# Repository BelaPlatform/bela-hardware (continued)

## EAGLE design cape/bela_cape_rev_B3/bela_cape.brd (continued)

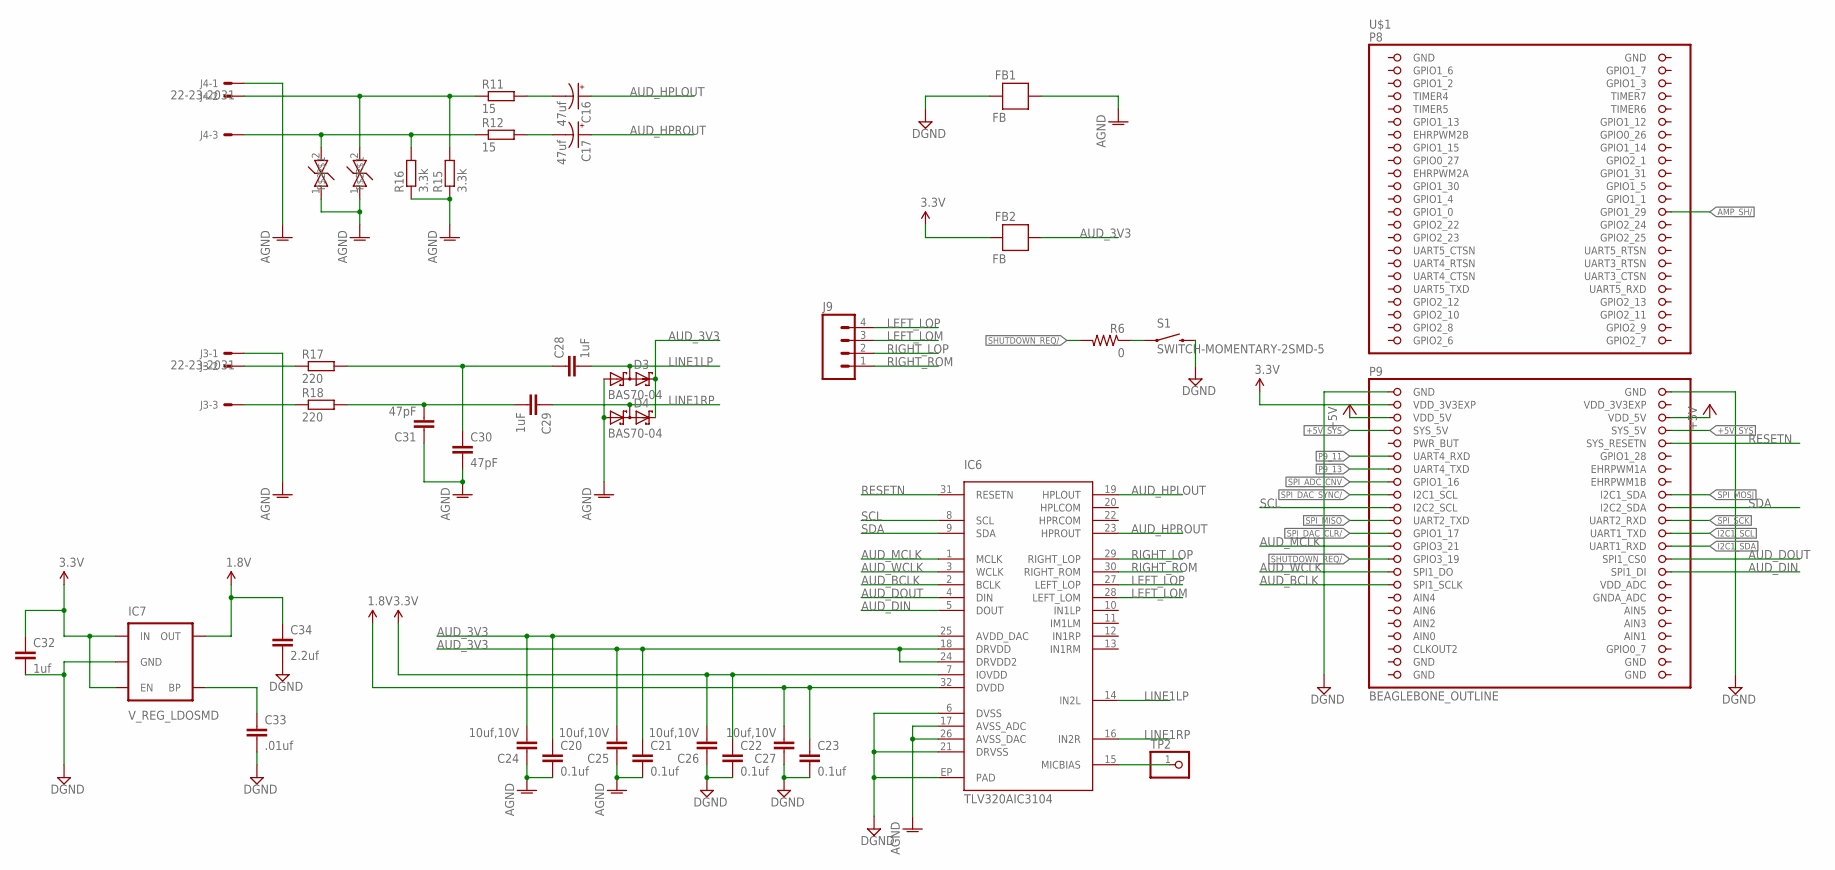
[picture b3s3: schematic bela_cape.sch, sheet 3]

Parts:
C16, C17: 47uf; EIA3216
C20, C21, C22, C23: 0.1uf; C0603
C24, C25, C26, C27: 10uf,10V; 0603-CAP
C28, C29: 1uF; C0603
C30, C31: 47pF; C0603
C32: 1uf; C0603
C33: .01uf; C0603
C34: 2.2uf; C0603
D1, D2: PGB0010603MR; 0603
D3, D4: BAS70-04; SOT23
FB1, FB2: FB; 0603
IC6: TLV320AIC3104; QFN-32
IC7: V_REG_LDOSMD; SOT23-5
J3, J4: 22-23-2031
J9: M04PTH; 1X04
R6: 0; R0603
R11, R12: 15; R0603
R15, R16: 3.3k; R0603
R17, R18: 220; R0603
S1: SWITCH-MOMENTARY-2SMD-5; TACTILE_SWITCH_SMD-4
TP2: PINHD-1X1; 1X01
U$1: BEAGLEBONE_OUTLINE; BEAGLEBONE_SHIELD

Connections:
1.8V: C23.1, C27.2, C34.1, IC6.32 (DVDD), IC7.5 (OUT)
3.3V: C22.1, C26.2, C32.1, FB2.2, IC6.7 (IOVDD), IC7.1 (IN), IC7.3 (EN), U$1.49 (VDD_3V3EXP); also elsewhere on the board
+5V_POW: U$1.51 (VDD_5V), U$1.52 (VDD_5V); also elsewhere on the board
+5V_SYS: U$1.53 (SYS_5V), U$1.54 (SYS_5V); also elsewhere on the board
AGND: C20.2, C21.2, C24.1, C25.1, C30.2, C31.1, D1.1, D2.1, D3.1 (A1), D4.1 (A1), FB1.1, IC6.17 (AVSS_ADC), IC6.26 (AVSS_DAC), J3.1, J4.1, R15.1, R16.1; also elsewhere on the board
AIN0: U$1.85 (AIN0)
AMP_SH/: U$1.26 (GPIO1_29); also elsewhere on the board
AUDIO_INL: C28.1, C30.1, R17.2
AUDIO_INR: C29.2, C31.2, R18.2
AUD_3V3: C20.1, C21.1, C24.2, C25.2, D3.2 (C2), D4.2 (C2), FB2.1, IC6.18 (DRVDD), IC6.24 (DRVDD2), IC6.25 (AVDD_DAC)
AUD_BCLK: IC6.2 (BCLK), U$1.77 (SPI1_SCLK)
AUD_DIN: IC6.5 (DOUT), U$1.76 (SPI1_DI)
AUD_DOUT: IC6.4 (DIN), U$1.74 (SPI1_CS0)
AUD_HPLOUT: C16.A (+), IC6.19 (HPLOUT)
AUD_HPROUT: C17.A (+), IC6.23 (HPROUT)
AUD_MCLK: IC6.1 (MCLK), U$1.71 (GPIO3_21)
AUD_WCLK: IC6.3 (WCLK), U$1.75 (SPI1_DO)
DGND: C22.2, C23.2, C26.1, C27.1, C32.2, C33.2, C34.2, FB1.2, IC6.6 (DVSS), IC6.21 (DRVSS), IC6.EP (PAD), IC7.2 (GND), S1.4 (2), U$1.1 (GND), U$1.2 (GND), U$1.47 (GND), U$1.48 (GND), U$1.89 (GND), U$1.90 (GND), U$1.91 (GND), U$1.92 (GND); also elsewhere on the board
HPL: D2.2, J4.2, R11.1, R15.2
HPR: D1.2, J4.3, R12.1, R16.2
I2C1_SCL: U$1.70 (UART1_TXD); also elsewhere on the board
I2C1_SDA: U$1.72 (UART1_RXD); also elsewhere on the board
LEFT_LOM: IC6.28 (LEFT_LOM), J9.3
LEFT_LOP: IC6.27 (LEFT_LOP), J9.4
LINE1LP: C28.2, D3.3 (C1A2), IC6.14 (IN2L)
LINE1RP: C29.1, D4.3 (C1A2), IC6.16 (IN2R)
unnamed: C16.C (-), R11.2
unnamed: IC6.15 (MICBIAS), TP2.1
unnamed: R6.1, S1.1
unnamed: C17.C (-), R12.2
unnamed: J3.2, R17.1
unnamed: C33.1, IC7.4 (BP)
unnamed: J3.3, R18.1
P9_11: U$1.57 (UART4_RXD)
P9_13: U$1.59 (UART4_TXD)
RESETN: IC6.31 (RESETN), U$1.56 (SYS_RESETN)
RIGHT_LOP: IC6.29 (RIGHT_LOP), J9.2
RIGHT_ROM: IC6.30 (RIGHT_ROM), J9.1
SCL: IC6.8 (SCL), U$1.65 (I2C2_SCL)
SDA: IC6.9 (SDA), U$1.66 (I2C2_SDA)
SHUTDOWN_REQ/: R6.2, U$1.73 (GPIO3_19)
SPI_ADC_CNV: U$1.61 (GPIO1_16); also elsewhere on the board
SPI_DAC_CLR/: U$1.69 (GPIO1_17); also elsewhere on the board
SPI_DAC_SYNC/: U$1.63 (I2C1_SCL); also elsewhere on the board
SPI_MISO: U$1.67 (UART2_TXD); also elsewhere on the board
SPI_MOSI: U$1.64 (I2C1_SDA); also elsewhere on the board
SPI_SCK: U$1.68 (UART2_RXD); also elsewhere on the board
VDD_3V3EXP: U$1.50 (VDD_3V3EXP)

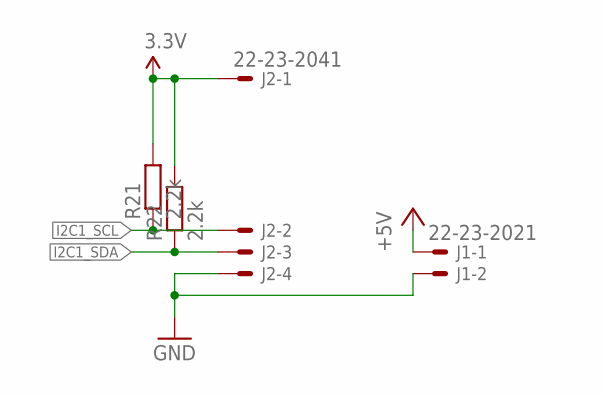
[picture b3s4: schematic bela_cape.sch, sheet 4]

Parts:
J1: 22-23-2021
J2: 22-23-2041
R21, R22: 2.2k; R0603

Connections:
3.3V: J2.1, R21.2, R22.2; also elsewhere on the board
+5V_AMP: J1.1; also elsewhere on the board
DGND: J1.2, J2.4; also elsewhere on the board
I2C1_SCL: J2.2, R21.1; also elsewhere on the board
I2C1_SDA: J2.3, R22.1; also elsewhere on the board

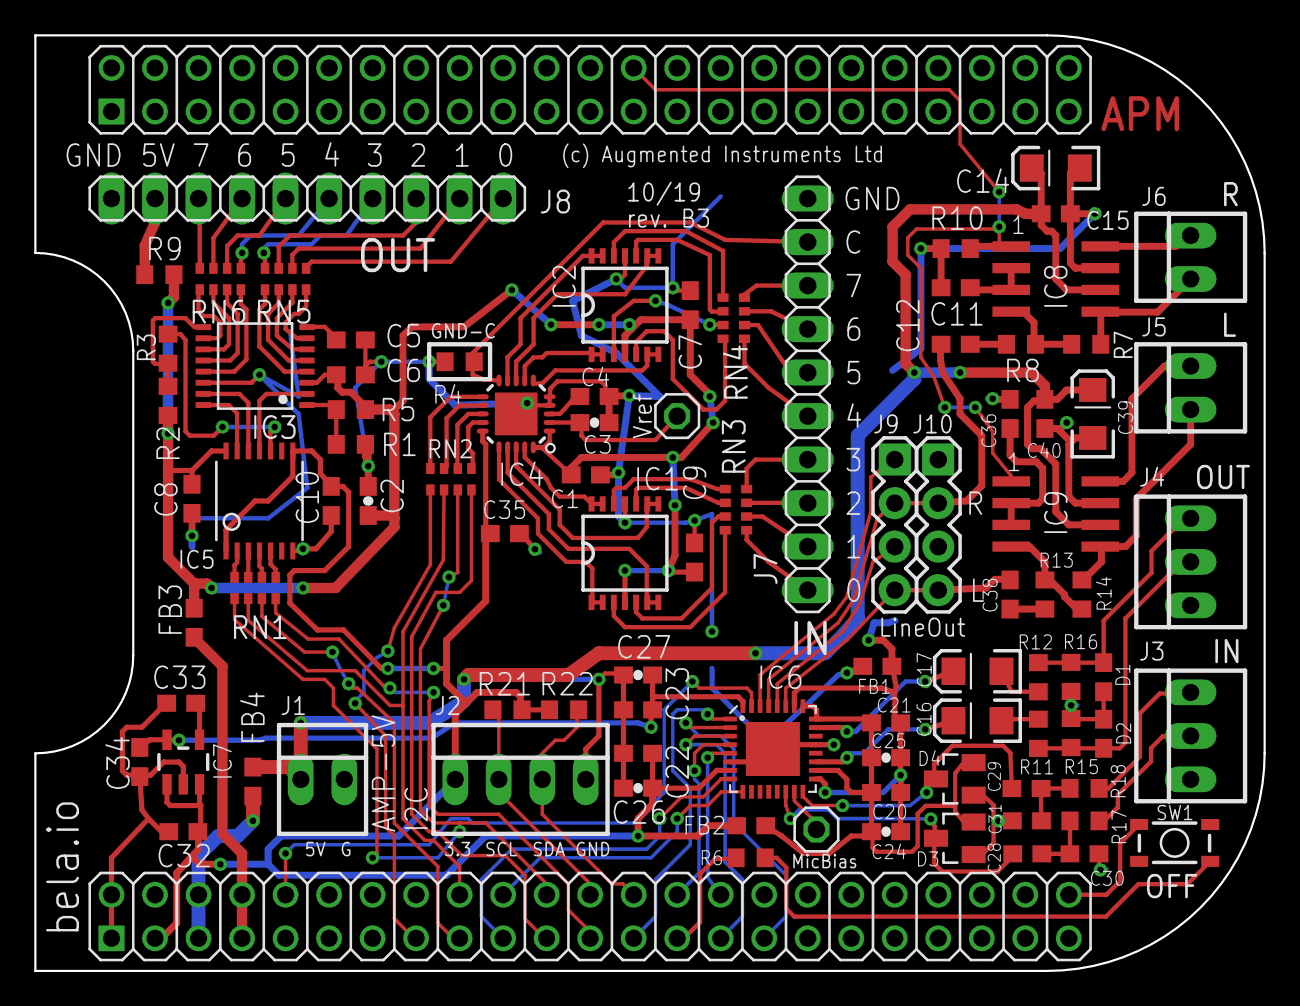
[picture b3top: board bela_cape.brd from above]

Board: 2 copper layers, 71.8 x 54.6 mm, 93 parts (0 on the bottom side), 117 nets.

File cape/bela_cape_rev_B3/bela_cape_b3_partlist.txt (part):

Partlist

Exported from bela_cape.brd at 09/12/2019 12:21

EAGLE Version 6.5.0 Copyright (c) 1988-2013 CadSoft

Assembly variant: 

Part     Value                   Package              Library             Position (inch)       Orientation

C1       0.1uF                   C0603                rcl                 (1.03 -1.71)          R0
C2       10uF                    0603-CAP             SparkFun-Passives   (0.53 -1.77)          R90
C3       10uF                    0603-CAP             SparkFun-Passives   (1.05 -1.59)          R0
C4       0.1uF                   C0603                rcl                 (1.05 -1.53)          R0
C5       0.1uF                   C0603                rcl                 (0.49 -1.4)           R0
C6       0.1uF                   C0603                rcl                 (0.49 -1.48)          R0
C7       0.1uF                   C0603                rcl                 (1.27 -1.32)          R90
C8       0.1uF                   C0603                rcl                 (0.125 -1.765)        R270
C9       0.1uF                   C0603                rcl                 (1.28 -1.9)           R90
C10      0.1uF                   C0603                rcl                 (0.445 -1.77)         R270
C11      0.1uF                   C0603                rcl                 (1.88 -1.28)          R180
C12      1uF                     C0603                rcl                 (1.88 -1.41)          R0
C14      47uF                    EIA3216              SparkFun-Capacitors (2.11 -1.005)         R180
C15      0.1uF                   C0603                rcl                 (2.11 -1.11)          R0
C16      47uf                    EIA3216              SparkFun-Capacitors (1.93 -2.27500209)    R180
C17      47uf                    EIA3216              SparkFun-Capacitors (1.93 -2.16136602)    R180
C20      0.1uf                   C0603                rcl                 (1.72 -2.44)          R0
C21      0.1uf                   C0603                rcl                 (1.72 -2.28)          R0
C22      0.1uf                   C0603                rcl                 (1.15 -2.35)          R180
C23      0.1uf                   C0603                rcl                 (1.15 -2.25)          R180
C24      10uf,10V                0603-CAP             SparkFun-Passives   (1.72 -2.53)          R180
C25      10uf,10V                0603-CAP             SparkFun-Passives   (1.72 -2.36)          R180
C26      10uf,10V                0603-CAP             SparkFun-Passives   (1.15 -2.43)          R0
C27      10uf,10V                0603-CAP             SparkFun-Passives   (1.15 -2.17)          R0
C28      1uF                     C0603                rcl                 (2.04452817 -2.58090391) R180
C29      1uF                     C0603                rcl                 (2.04271001 -2.43091191) R0
C30      47pF                    C0603                rcl                 (2.17589186 -2.58090404) R0
C31      47pF                    C0603                rcl                 (2.04368602 -2.50495792) R0
C32      1uf                     C0603                rcl                 (0.105 -2.53)         R180
C33      .01uf                   C0603                rcl                 (0.1 -2.235)          R180
C34      2.2uf                   C0603                rcl                 (0.005 -2.37)         R270
C35      0.1uF                   C0603                rcl                 (0.844 -1.845)        R0
C36      0.1uF                   C0603                rcl                 (2.005 -1.57)         R90
C38      1uF                     C0603                rcl                 (2.005 -1.985)        R90
C39      47uF                    EIA3216              SparkFun-Capacitors (2.195 -1.57)         R90
C40      0.1uF                   C0603                rcl                 (2.085 -1.57)         R270
D1       PGB0010603MR            0603                 CircuitCo           (2.22 -2.175)         R90
D2       PGB0010603MR            0603                 CircuitCo           (2.22 -2.305)         R270
D3       BAS70-04                SOT23                diode               (1.87799409 -2.54519993) R90
D4       BAS70-04                SOT23                diode               (1.87799409 -2.4088499) R90
FB1      FB                      0603                 SparkFun-Passives   (1.7 -2.15)           R180
FB2      FB                      0603                 SparkFun-Passives   (1.41 -2.5163659)     R180
FB3      FB                      0603                 SparkFun-Passives   (0.13 -2.05)          R270
FB4      FB                      0603                 SparkFun-Passives   (0.265 -2.415)        R90
IC1      ADD8704RU               TSSOP14              analog-devices      (1.12 -1.89)          R90
IC2      ADD8704RU               TSSOP14              analog-devices      (1.12 -1.32)          R90
IC3      AD5668                  TSSOP16-PW           custom              (0.27 -1.46)          R90
IC4      AD7699                  LFCSP20-LEADS        custom              (0.87 -1.57)          R180
IC5                              TSSOP14              SparkFun-DigitalIC  (0.28 -1.77)          R0
IC6      TLV320AIC3104           QFN-32               CircuitCo           (1.46 -2.34)          R270
IC7      V_REG_LDOSMD            SOT23-5              SparkFun-PowerIC    (0.105 -2.37)         R0
IC8      LM4876                  SO8                  custom              (2.11 -1.26)          R270
IC9      LM4876                  SO8                  custom              (2.11 -1.8)           R270
J1       22-23-2021              22-23-2021           con-molex           (0.425 -2.41)         R0
J2       22-23-2041              22-23-2041           con-molex           (0.88 -2.41)          R0
J3       22-23-2031              22-23-2031           con-molex           (2.42 -2.31)          R90
J4       22-23-2031              22-23-2031           con-molex           (2.42 -1.91)          R90
J5       22-23-2021              22-23-2021           con-molex           (2.42 -1.51)          R90
J6       22-23-2021              22-23-2021           con-molex           (2.42 -1.21)          R90
J7                               1X10                 pinhead             (1.54 -1.525)         R90
J8                               1X10                 pinhead             (0.39 -1.075)         R180
J9                               1X04                 SparkFun-Connectors (1.74 -1.675)         R270
J10                              1X04                 SparkFun-Connectors (1.84 -1.675)         R270
R1       0                       R0603                rcl                 (0.49 -1.64)          R0
R2       0                       R0603                rcl                 (0.07 -1.54)          R90
R3       DNI                     R0603                rcl                 (0.07 -1.42)          R270
R4       0                       R0603                rcl                 (0.74 -1.45)          R0
R5       DNI                     R0603                rcl                 (0.49 -1.56)          R180
R6       0                       R0603                rcl                 (1.40872281 -2.59002178) R180
R7       43k                     R0603                rcl                 (2.18 -1.41)          R180
R8       22k                     R0603                rcl                 (2.03 -1.41)          R180
R9       100                     R0603                rcl                 (0.05 -1.25)          R0
R10      22k                     R0603                rcl                 (1.88 -1.19)          R180
R11      15                      R0603                rcl                 (2.07 -2.305)         R90
R12      15                      R0603                rcl                 (2.07 -2.175)         R270
R13      22k                     R0603                rcl                 (2.085 -1.985)        R270
R14      43k                     R0603                rcl                 (2.17 -1.985)         R270
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
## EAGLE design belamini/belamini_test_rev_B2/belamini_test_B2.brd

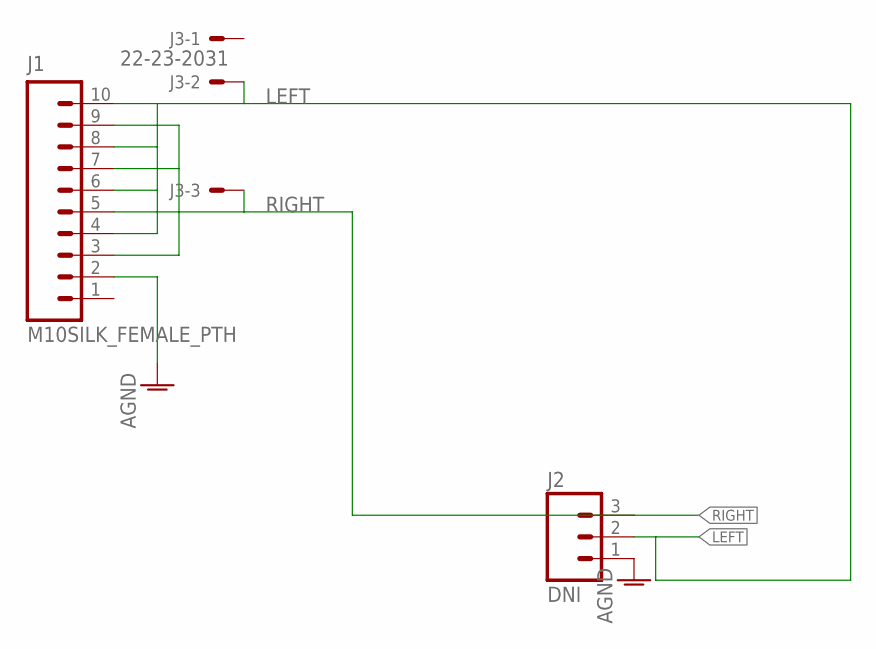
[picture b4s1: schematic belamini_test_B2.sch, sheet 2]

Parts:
J1: M10SILK_FEMALE_PTH; 1X10
J2: DNI; 1X03
J3: 22-23-2031

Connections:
AGND: J1.2
GND: J2.1
LEFT: J1.4, J1.6, J1.8, J1.10, J2.2, J3.2
RIGHT: J1.3, J1.5, J1.7, J1.9, J2.3, J3.3

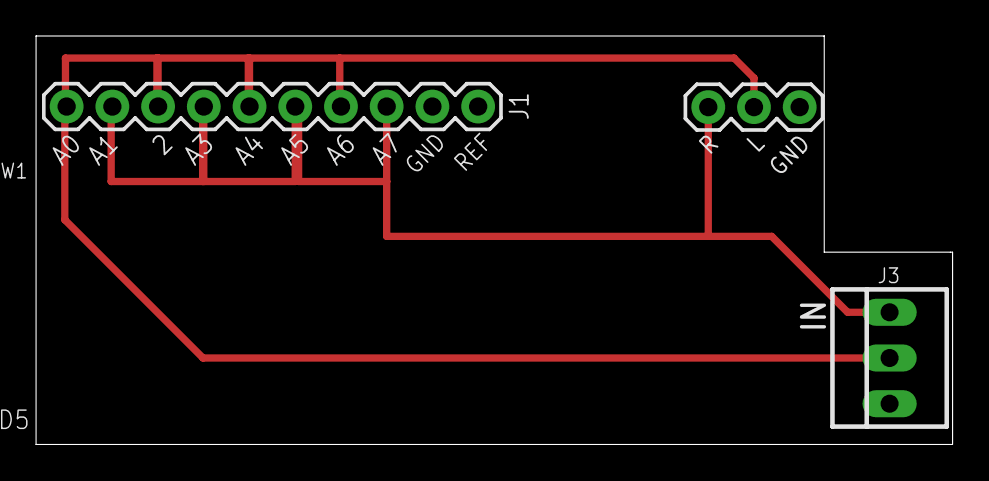
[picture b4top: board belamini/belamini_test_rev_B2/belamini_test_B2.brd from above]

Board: 2 copper layers, 50.9 x 22.7 mm, 3 parts (0 on the bottom side), 2 nets.

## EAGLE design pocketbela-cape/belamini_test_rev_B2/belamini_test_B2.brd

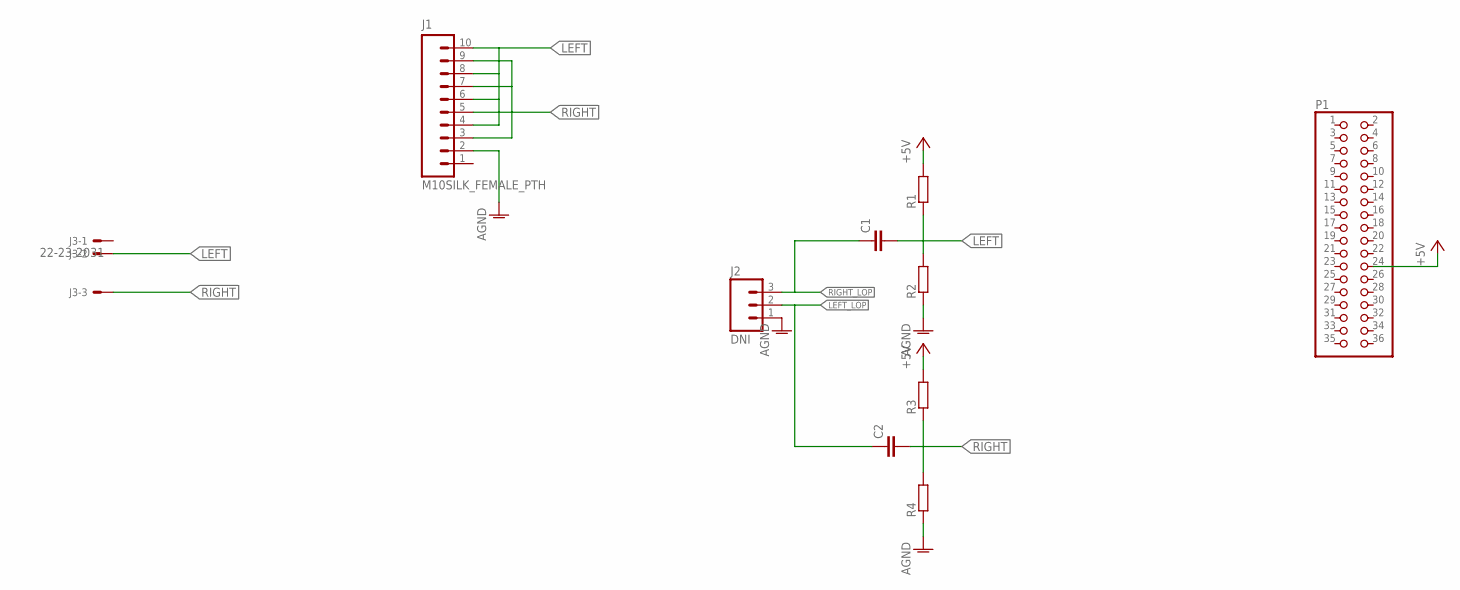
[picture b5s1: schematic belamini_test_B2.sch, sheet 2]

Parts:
C1, C2: C5/2.5; C5B2.5
J1: M10SILK_FEMALE_PTH; 1X10
J2: DNI; 1X03
J3: 22-23-2031
P1: PINHD-2X18; 2X18
R1, R2, R3, R4: R-EU_0204/7; 0204/7

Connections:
+5V_SYS: P1.24, R1.2, R3.2
AGND: J1.2, R2.1, R4.1
GND: J2.1
LEFT: C1.2, J1.4, J1.6, J1.8, J1.10, J3.2, R1.1, R2.2
LEFT_LOP: C2.1, J2.2
RIGHT: C2.2, J1.3, J1.5, J1.7, J1.9, J3.3, R3.1, R4.2
RIGHT_LOP: C1.1, J2.3

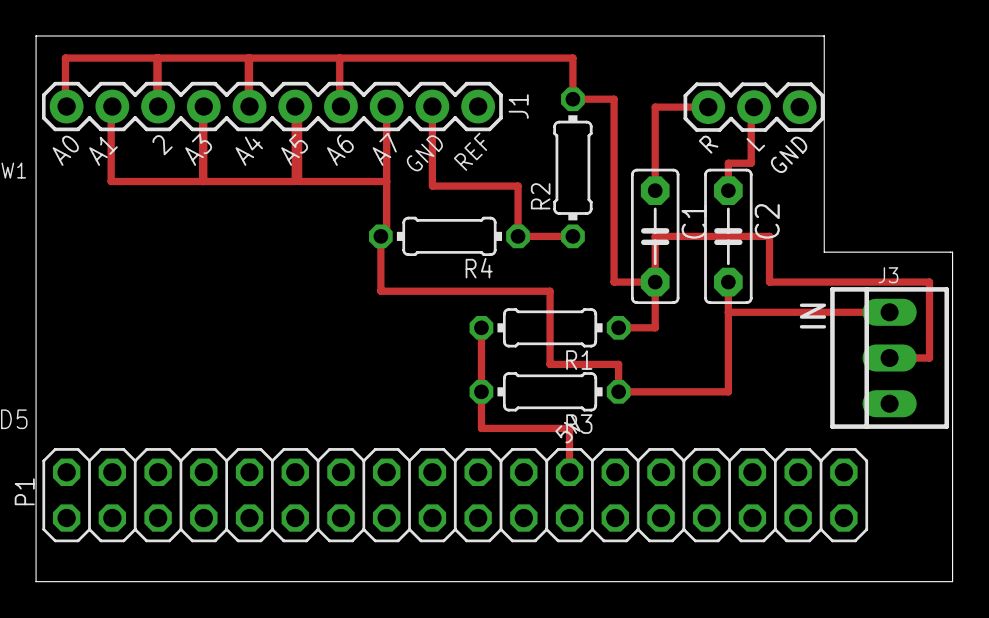
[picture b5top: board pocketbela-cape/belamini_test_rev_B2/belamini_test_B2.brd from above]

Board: 2 copper layers, 50.9 x 30.3 mm, 10 parts (0 on the bottom side), 6 nets.

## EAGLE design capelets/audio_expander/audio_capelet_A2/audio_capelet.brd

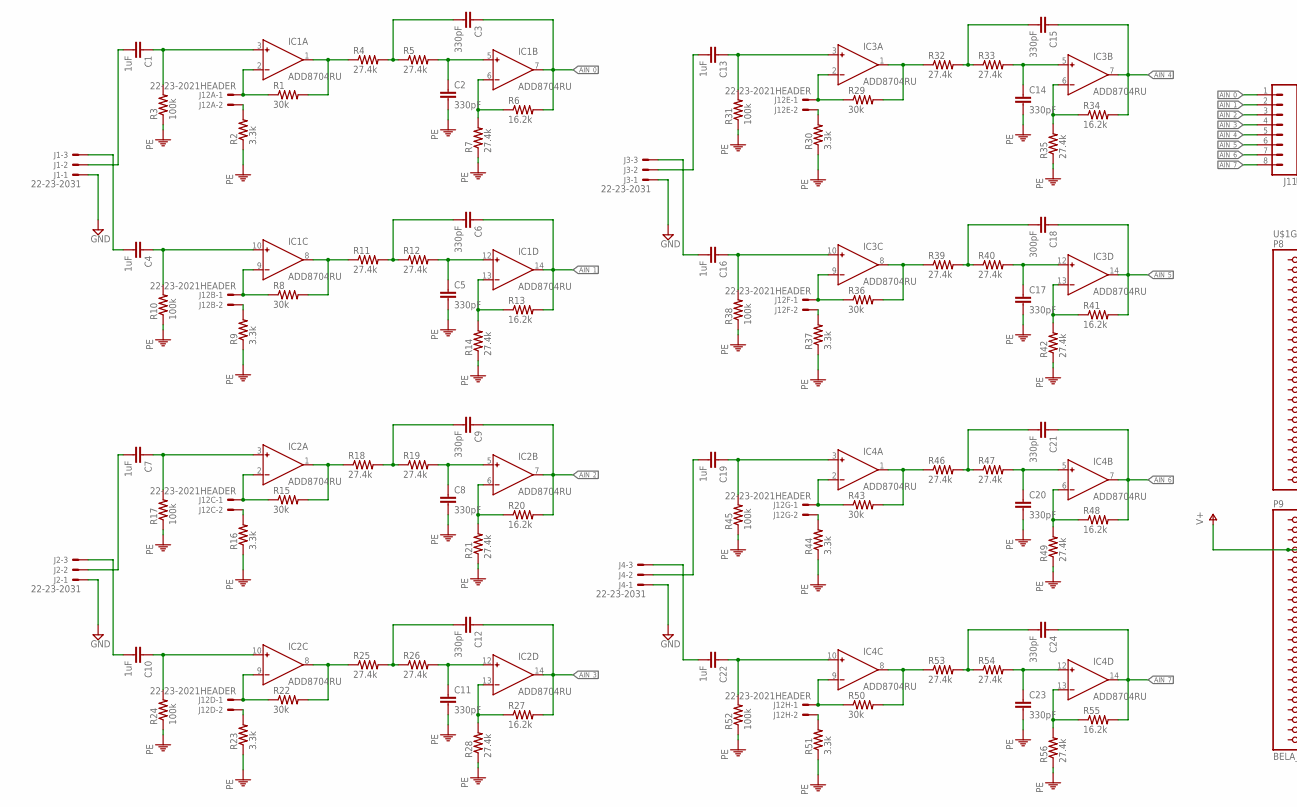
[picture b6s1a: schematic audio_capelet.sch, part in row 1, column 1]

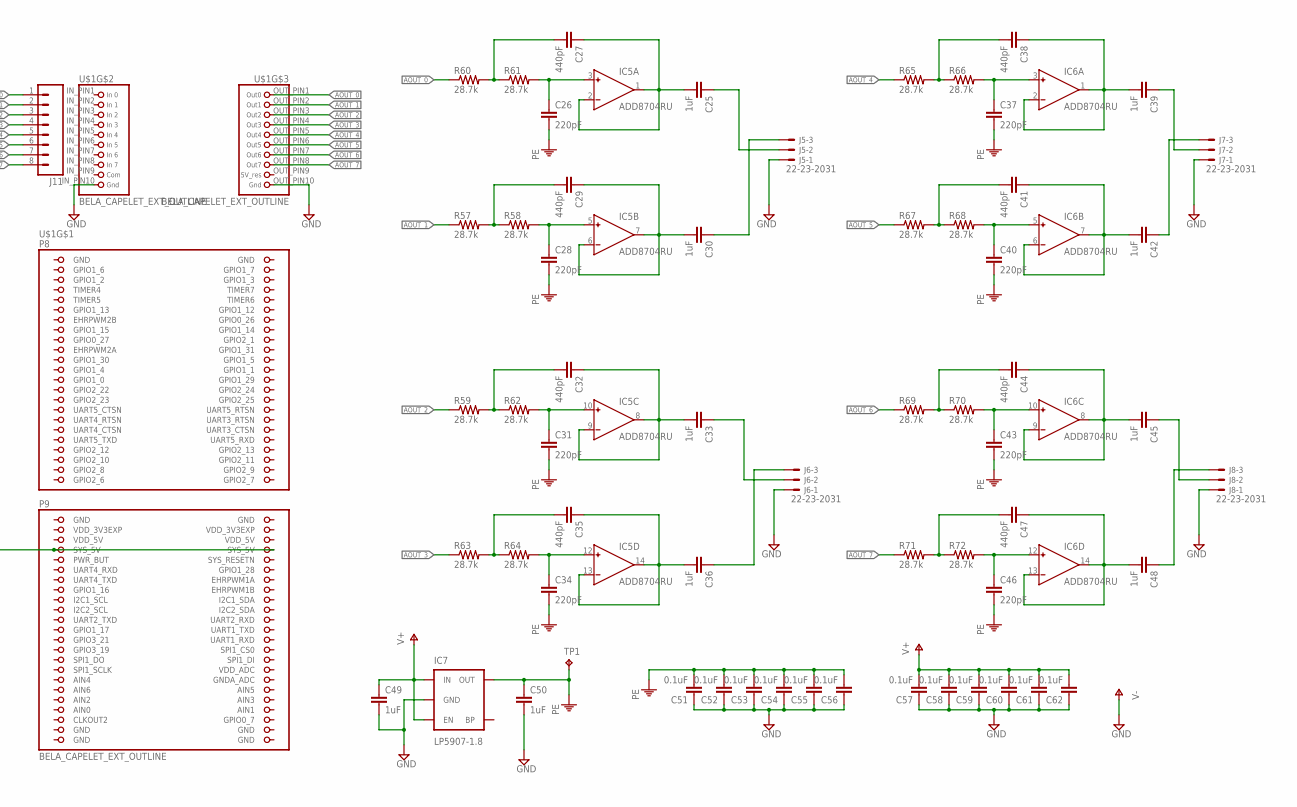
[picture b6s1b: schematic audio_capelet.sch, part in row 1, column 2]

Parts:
C1, C4, C7, C10, C13, C16, C19, C22, C25, C30, C33, C36, C39, C42, C45, C48, C49, C50: 1uF; C0603
C2, C3, C5, C6, C8, C9, C11, C12, C14, C15, C17, C20, C21, C23, C24: 330pF; C0603
C18: 300pF; C0603
C26, C28, C31, C34, C37, C40, C43, C46: 220pF; C0603
C27, C29, C32, C35, C38, C41, C44, C47: 440pF; C0603
C51, C52, C53, C54, C55, C56, C57, C58, C59, C60, C61, C62: 0.1uF; C0603
IC1, IC2, IC3, IC4, IC5, IC6: ADD8704RU; TSSOP14
IC7: LP5907-1.8; SOT23-5
J1, J2, J3, J4, J5, J6, J7, J8: 22-23-2031
J11: M08SMALL_DIAMETER; 1X08_SMALL_DIAMETER
J12A, J12B, J12C, J12D, J12E, J12F, J12G, J12H: 22-23-2021HEADER; 1X02
R1, R8, R15, R22, R29, R36, R43, R50: 30k; R0603
R2, R9, R16, R23, R30, R37, R44, R51: 3.3k; R0603
R3, R10, R17, R24, R31, R38, R45, R52: 100k; R0603
R4, R5, R7, R11, R12, R14, R18, R19, R21, R25, R26, R28, R32, R33, R35, R39, R40, R42, R46, R47, R49, R53, R54, R56: 27.4k; R0603
R6, R13, R20, R27, R34, R41, R48, R55: 16.2k; R0603
R57, R58, R59, R60, R61, R62, R63, R64, R65, R66, R67, R68, R69, R70, R71, R72: 28.7k; R0603
TP1: TPPAD1-17Y; P1-17Y
U$1: BELA_CAPELET_EXT_OUTLINE; BELA_CAPELET_EXTENDED_OUTLINE

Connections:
01: C30.1, J5.3
AIN0: U$1.85 (AIN0)
AIN_0: C3.1, IC1.7 (OUT), J11.1, R6.2
AIN_1: C6.1, IC1.14 (OUT), J11.2, R13.2
AIN_2: C9.1, IC2.7 (OUT), J11.3, R20.2
AIN_3: C12.1, IC2.14 (OUT), J11.4, R27.2
AIN_4: C15.1, IC3.7 (OUT), J11.5, R34.2
AIN_5: C18.1, IC3.14 (OUT), J11.6, R41.2
AIN_6: C21.1, IC4.7 (OUT), J11.7, R48.2
AIN_7: C24.1, IC4.14 (OUT), J11.8, R55.2
AOUT_0: R60.1, U$1.OUT_PIN1 (1)
AOUT_1: R57.1, U$1.OUT_PIN2 (2)
AOUT_2: R59.1, U$1.OUT_PIN3 (3)
AOUT_3: R63.1, U$1.OUT_PIN4 (4)
AOUT_4: R65.1, U$1.OUT_PIN5 (5)
AOUT_5: R67.1, U$1.OUT_PIN6 (6)
AOUT_6: R69.1, U$1.OUT_PIN7 (7)
AOUT_7: R71.1, U$1.OUT_PIN8 (8)
unnamed: C2.1, IC1.5 (IN+), R5.2
unnamed: IC1.2 (IN-), J12A.1, R1.1
unnamed: IC1.1 (OUT), R1.2, R4.1
unnamed: C3.2, R4.2, R5.1
unnamed: C25.2, C27.1, IC5.1 (OUT), IC5.2 (IN-)
unnamed: IC1.6 (IN-), R6.1, R7.2
unnamed: C1.1, IC1.3 (IN+), R3.2
unnamed: J12A.2, R2.2
unnamed: IC1.8 (OUT), R8.2, R11.1
unnamed: C6.2, R11.2, R12.1
unnamed: C5.1, IC1.12 (IN+), R12.2
unnamed: C27.2, R60.2, R61.1
unnamed: IC1.13 (IN-), R13.1, R14.2
unnamed: IC2.1 (OUT), R15.2, R18.1
unnamed: C4.1, IC1.10 (IN+), R10.2
unnamed: IC1.9 (IN-), J12B.1, R8.1
unnamed: C1.2, J1.2
unnamed: C4.2, J1.3
unnamed: IC2.2 (IN-), J12C.1, R15.1
unnamed: C9.2, R18.2, R19.1
unnamed: C8.1, IC2.5 (IN+), R19.2
unnamed: C26.1, IC5.3 (IN+), R61.2
unnamed: IC2.6 (IN-), R20.1, R21.2
unnamed: J12C.2, R16.2
unnamed: C7.1, IC2.3 (IN+), R17.2
unnamed: IC2.8 (OUT), R22.2, R25.1
unnamed: C12.2, R25.2, R26.1
unnamed: C11.1, IC2.12 (IN+), R26.2
unnamed: C29.2, R57.2, R58.1
unnamed: IC2.13 (IN-), R27.1, R28.2
unnamed: IC2.9 (IN-), J12D.1, R22.1
unnamed: J12D.2, R23.2
unnamed: C10.1, IC2.10 (IN+), R24.2
unnamed: C7.2, J2.2
unnamed: C10.2, J2.3
unnamed: IC3.1 (OUT), R29.2, R32.1
unnamed: C15.2, R32.2, R33.1
unnamed: C14.1, IC3.5 (IN+), R33.2
unnamed: C28.1, IC5.5 (IN+), R58.2
unnamed: IC3.6 (IN-), R34.1, R35.2
unnamed: C13.1, IC3.3 (IN+), R31.2
unnamed: IC3.2 (IN-), J12E.1, R29.1
unnamed: J12E.2, R30.2
unnamed: IC3.8 (OUT), R36.2, R39.1
unnamed: C18.2, R39.2, R40.1
unnamed: C17.1, IC3.12 (IN+), R40.2
unnamed: C29.1, C30.2, IC5.6 (IN-), IC5.7 (OUT)
unnamed: IC3.13 (IN-), R41.1, R42.2
unnamed: C16.1, IC3.10 (IN+), R38.2
unnamed: IC3.9 (IN-), J12F.1, R36.1
unnamed: J12F.2, R37.2
unnamed: C13.2, J3.2
unnamed: C16.2, J3.3
unnamed: IC4.1 (OUT), R43.2, R46.1
unnamed: C21.2, R46.2, R47.1
unnamed: C20.1, IC4.5 (IN+), R47.2
unnamed: C32.2, R59.2, R62.1
unnamed: IC4.6 (IN-), R48.1, R49.2
unnamed: C19.1, IC4.3 (IN+), R45.2
unnamed: IC4.2 (IN-), J12G.1, R43.1
unnamed: J12G.2, R44.2
unnamed: IC4.8 (OUT), R50.2, R53.1
unnamed: C24.2, R53.2, R54.1
unnamed: C23.1, IC4.12 (IN+), R54.2
unnamed: C31.1, IC5.10 (IN+), R62.2
unnamed: IC4.13 (IN-), R55.1, R56.2
unnamed: C22.1, IC4.10 (IN+), R52.2
unnamed: IC4.9 (IN-), J12H.1, R50.1
unnamed: J12H.2, R51.2
unnamed: C19.2, J4.2
unnamed: C22.2, J4.3
unnamed: C32.1, C33.2, IC5.8 (OUT), IC5.9 (IN-)
unnamed: C35.2, R63.2, R64.1
unnamed: C34.1, IC5.12 (IN+), R64.2
unnamed: C35.1, C36.2, IC5.13 (IN-), IC5.14 (OUT)
unnamed: C38.2, R65.2, R66.1
unnamed: C37.1, IC6.3 (IN+), R66.2
unnamed: J12B.2, R9.2
unnamed: C38.1, C39.2, IC6.1 (OUT), IC6.2 (IN-)
unnamed: C41.2, R67.2, R68.1
unnamed: C40.1, IC6.5 (IN+), R68.2
unnamed: C41.1, C42.2, IC6.6 (IN-), IC6.7 (OUT)
unnamed: C44.2, R69.2, R70.1
unnamed: C43.1, IC6.10 (IN+), R70.2
unnamed: C44.1, C45.2, IC6.8 (OUT), IC6.9 (IN-)
unnamed: C47.2, R71.2, R72.1
unnamed: C46.1, IC6.12 (IN+), R72.2
unnamed: C47.1, C48.2, IC6.13 (IN-), IC6.14 (OUT)
unnamed: C45.1, J8.2
unnamed: C39.1, J7.2
O0: C25.1, J5.2
O2: C33.1, J6.2
O3: C36.1, J6.3
O5: C42.1, J7.3
O7: C48.1, J8.3
PE: C2.2, C5.2, C8.2, C11.2, C14.2, C17.2, C20.2, C23.2, C26.2, C28.2, C31.2, C34.2, C37.2, C40.2, C43.2, C46.2, C50.1, C51.2, C52.2, C53.2, C54.2, C55.2, C56.2, IC7.5 (OUT), R2.1, R3.1, R7.1, R9.1, R10.1, R14.1, R16.1, R17.1, R21.1, R23.1, R24.1, R28.1, R30.1, R31.1, R35.1, R37.1, R38.1, R42.1, R44.1, R45.1, R49.1, R51.1, R52.1, R56.1, TP1.TP
V+: C49.1, C57.2, C58.2, C59.2, C60.2, C61.2, C62.2, IC1.4 (V+), IC2.4 (V+), IC3.4 (V+), IC4.4 (V+), IC5.4 (V+), IC6.4 (V+), IC7.1 (IN), IC7.3 (EN), U$1.53 (SYS_5V), U$1.54 (SYS_5V)
V-: C49.2, C50.2, C51.1, C52.1, C53.1, C54.1, C55.1, C56.1, C57.1, C58.1, C59.1, C60.1, C61.1, C62.1, IC1.11 (V-), IC2.11 (V-), IC3.11 (V-), IC4.11 (V-), IC5.11 (V-), IC6.11 (V-), IC7.2 (GND), J1.1, J2.1, J3.1, J4.1, J5.1, J6.1, J7.1, J8.1, U$1.1 (GND), U$1.2 (GND), U$1.47 (GND), U$1.48 (GND), U$1.89 (GND), U$1.90 (GND), U$1.91 (GND), U$1.92 (GND), U$1.IN_PIN10 (10), U$1.OUT_PIN10 (10)
VDD_3V3EXP: U$1.49 (VDD_3V3EXP), U$1.50 (VDD_3V3EXP)
VDD_5V: U$1.51 (VDD_5V), U$1.52 (VDD_5V)

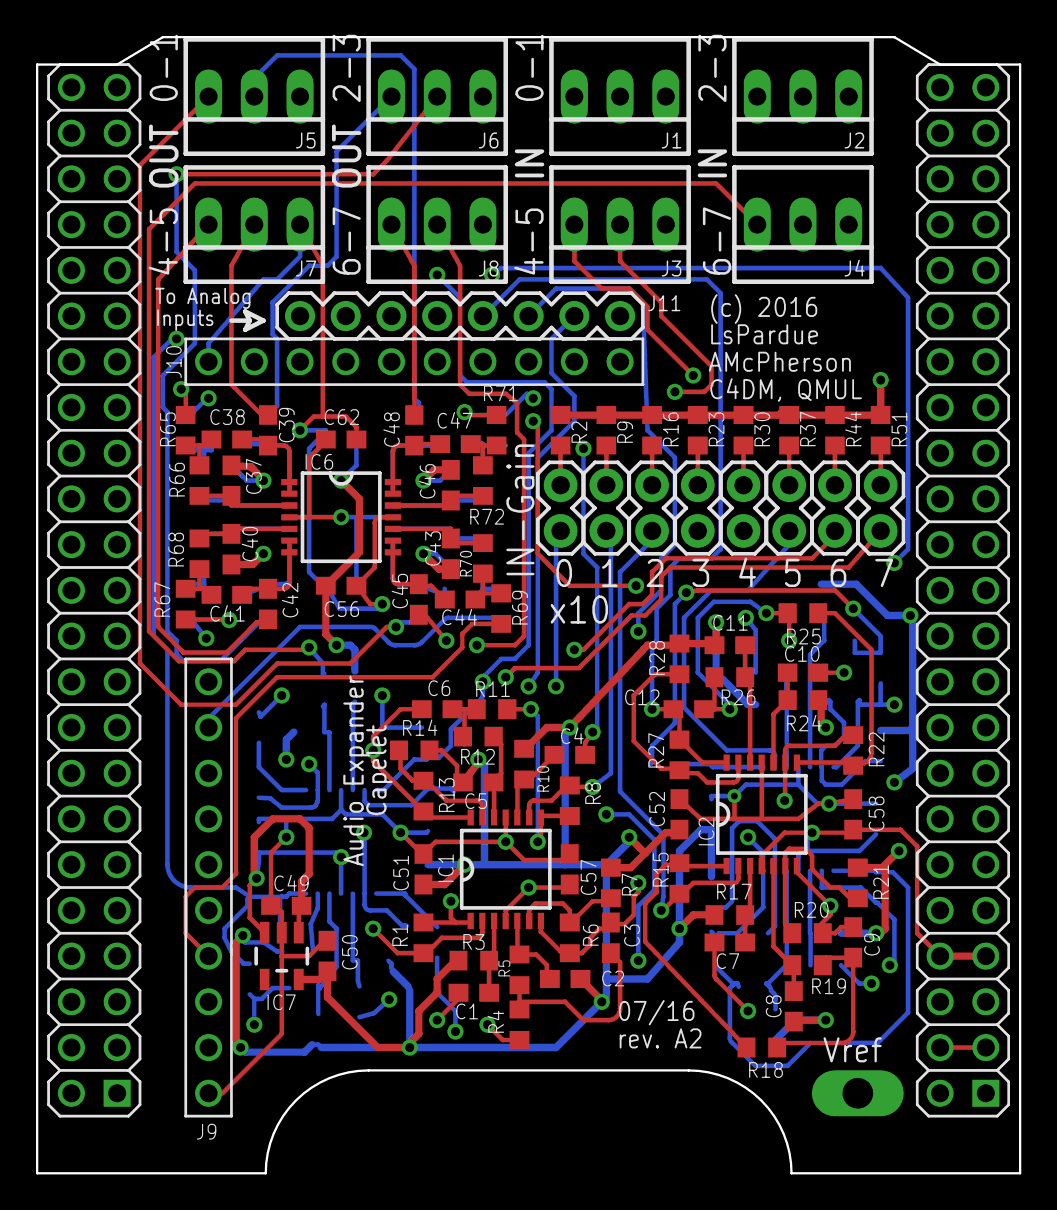
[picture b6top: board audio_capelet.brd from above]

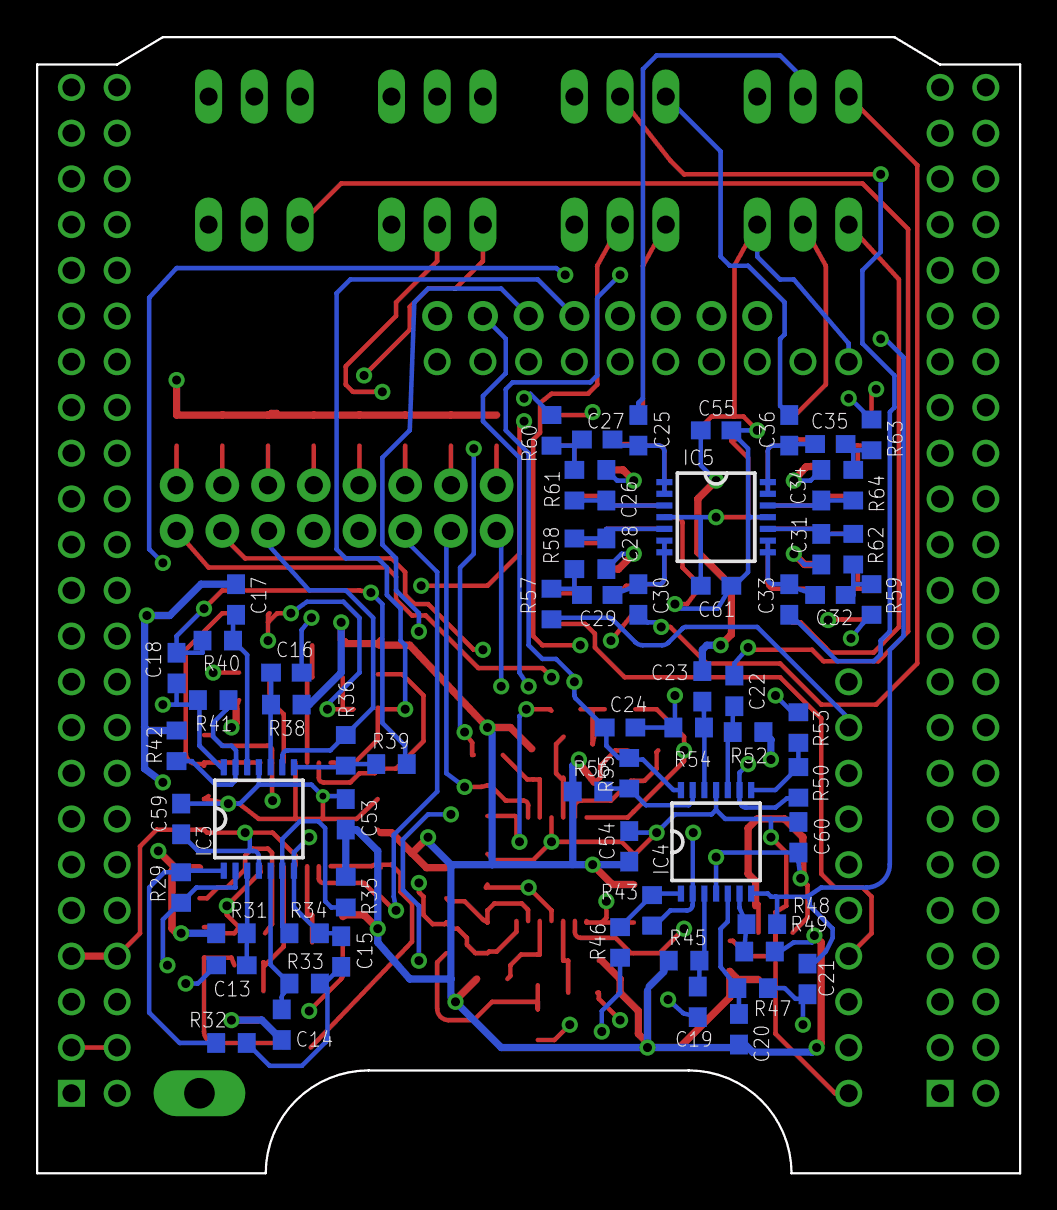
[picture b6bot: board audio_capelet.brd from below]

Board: 4 copper layers, 54.6 x 63.1 mm, 160 parts (65 on the bottom side), 117 nets.

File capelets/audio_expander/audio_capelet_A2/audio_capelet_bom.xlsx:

Name | Quantity | Value | Package | Description | Farnell # | Mouser # | Datasheet / Notes
C1, C4, C7, C10, C13, C16, C19, C22, C25, C30, C33, C36, C39, C42, C45, C48, C4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 | 18 | 1uF | “0603” | Capacitor ceramic 0603
C51-C62 | 12 | 0.1uF | “0603” | Capacitor ceramic 0603 | 1709957 | 80-C0603C104K5R
C2, C3, C5, C6, C8, C9, C11, C12, C14, C15, C17, C18, C20, C21, C23, C24 | 16 | 330pF | “0603” | Capacitor ceramic 0603, 5% or better tolerance
C26, C28, C31, C34, C37, C40, C43, C46 | 8 | 220pF | “0603” | Capacitor ceramic 0603, 5% or better tolerance
C27, C29, C32, C35, C38, C41, C44, C47 | 8 | 430pF | “0603” | Capacitor ceramic 0603, 5% or better tolerance
IC1-IC6 | 6 | OPA4348AIPWR | TSSOP-14 | Quad rail-to-rail op amp
IC7 | 1 | LP5907-MFX2.0 (or -MFX1.8) | SOT23-5 | Voltage regulator. 2.0V version is preferred but if it cannot be found, use LP5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 |  | 595-LP5907MFX-1.8NPB
J1-J8 | 8 | Molex 3-pin | Through Hole | 3-pin Molex KK series connector |  | 538-22-23-2031
J9-J10 | 2 | 10-pin socket | Through Hole | 10-pin socket with long tail leads, similar to P8/P9
J11 | 1 | 8-pin socket | Through Hole | 8-pin socket — SAME HEIGHT AS J10 — does not need long leads, but if needed to 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
J12 | 1 | 2x8 pin socket | Through Hole | 16-pin (2 row) female socket, 0.1” spacing
P8, P9 | 2 | Adafruit 706 (or similar) | Through Hole | 46-pin long-lead female sockets for BeagleBone |  |  | http://www.adafruit.com/product/706
R1, R8, R15, R22, R29, R36, R43, R50 | 8 | 30k ohm | “0603” | Resistor 0603 - 2% or better tolerance
R2, R9, R16, R23, R30, R37, R44, R51 | 8 | 3.3k ohm | “0603” | Resistor 0603 - 2% or better tolerance
R4, R5, R7, R11, R12, R14, R18, R19, R21, R25, R26, R28, R32, R33, R35, R39, R4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 | 24 | 27.4k ohm | “0603” | Resistor 0603 - 2% or better tolerance
R3, R10, R17, R24, R31, R38, R45, R52 | 8 | 100k ohm | “0603” | Resistor 0603
R6, R13, R20, R27, R34, R41, R48, R55 | 8 | 16.2k ohm | “0603” | Resistor 0603 - 2% or better tolerance
R57-R72 | 16 | 28.7k ohm | “0603” | Resistor 0603 - 2% or better tolerance
Total | 155 |  |  | Audio Expander Capelet rev. A2
